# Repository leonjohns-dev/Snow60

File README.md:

# Snow60

**SnowPad is a low profile 60% keyboard with choc v2 switches**

## CAD

- For the CAD, I am using Fusion 360 
- The CAD consists of a bottom case and a top plate, which are held together by 20 m2 screws and heat-inserts

| Altogether | Case |  Plate |
| --------------- | ------------- | ------------- | 
|  |  | 

## Shematic

- The MCU used for this project is a usb-c rasberry pi pico
- This is the shematic not for a PCB rather a diagram which can be used to hand wire the board

## PCB 

- This is a PCB designed specifically for RGB lighting for each key
- It is a single PCB board with V-cuts, which allows it to be split into multiple parts for each key
- Its single purpose is to hold RGB lights for each key while reducing the cost of making a single large PCB.

| PCB | Shematic |
| -------- | ------- |
|   |

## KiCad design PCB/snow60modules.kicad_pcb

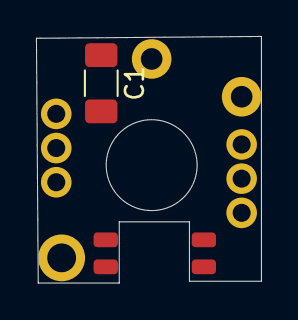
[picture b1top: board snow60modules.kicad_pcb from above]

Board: 2 copper layers, 12.5 x 13.7 mm, 7 parts (0 on the bottom side), 2 nets, no tracks yet.

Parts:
C1: C; C_1206_3216Metric_Pad1.33x1.80mm_HandSolder
TP1, TP2, TP3, TP4, TP5, TP6: TestPoint

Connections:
+5V: C1.1, TP2.1 (1_1), TP5.1 (1_1)
GND: C1.2, TP1.1 (1_1), TP4.1 (1_1)
